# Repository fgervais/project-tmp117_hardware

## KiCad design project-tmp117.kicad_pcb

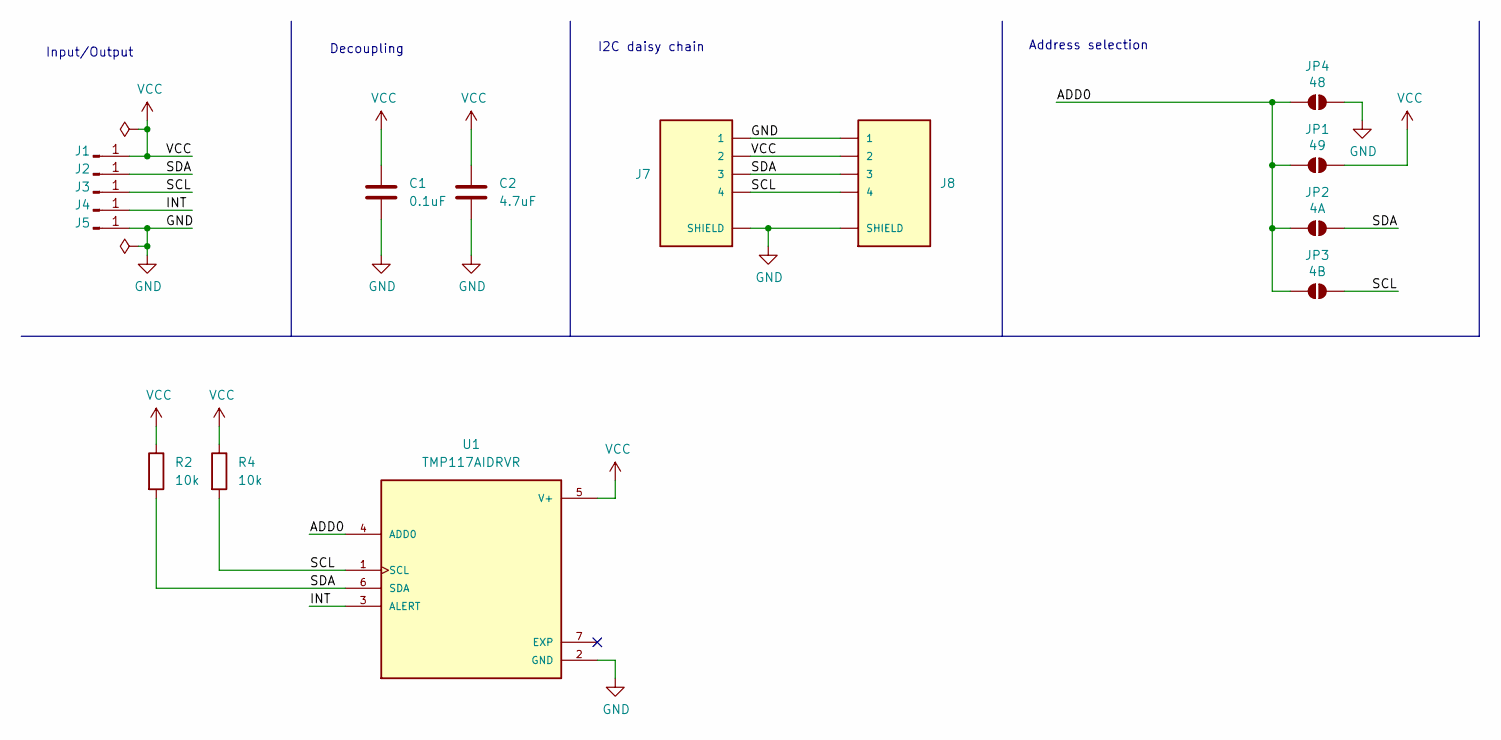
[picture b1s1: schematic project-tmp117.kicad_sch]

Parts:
C1: 0.1uF; C_0603_1608Metric
C2: 4.7uF; C_0805_2012Metric
J1, J2, J3, J4, J5: Conn_01x01_Pin; SolderWirePad_1x01_SMD_1x2mm
J7, J8: SM04B-SRSS-TB(LF)(SN); JST_SM04B-SRSS-TB(LF)(SN)
JP1: 49; SolderJumper-2_P1.3mm_Open_RoundedPad1.0x1.5mm
JP2: 4A; SolderJumper-2_P1.3mm_Open_RoundedPad1.0x1.5mm
JP3: 4B; SolderJumper-2_P1.3mm_Open_RoundedPad1.0x1.5mm
JP4: 48; SolderJumper-2_P1.3mm_Open_RoundedPad1.0x1.5mm
R2, R4: 10k; R_0603_1608Metric
U1: TMP117AIDRVR; SON65P200X200X80-7N; PARTREV B

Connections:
/ADD0: JP1.1 (A), JP2.1 (A), JP3.1 (A), JP4.1 (A), U1.4 (ADD0)
/INT: J4.1, U1.3 (ALERT)
/SCL: J3.1, J7.4, J8.4, JP3.2 (B), R4.2, U1.1 (SCL)
/SDA: J2.1, J7.3, J8.3, JP2.2 (B), R2.2, U1.6 (SDA)
GND: C1.2, C2.2, J5.1, J7.1, J7.S1 (SHIELD), J7.S2 (SHIELD), J8.1, J8.S1 (SHIELD), J8.S2 (SHIELD), JP4.2 (B), U1.2 (GND)
VCC: C1.1, C2.1, J1.1, J7.2, J8.2, JP1.2 (B), R2.1, R4.1, U1.5 (V+)

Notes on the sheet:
Address selection
Input/Output
I2C daisy chain
Decoupling

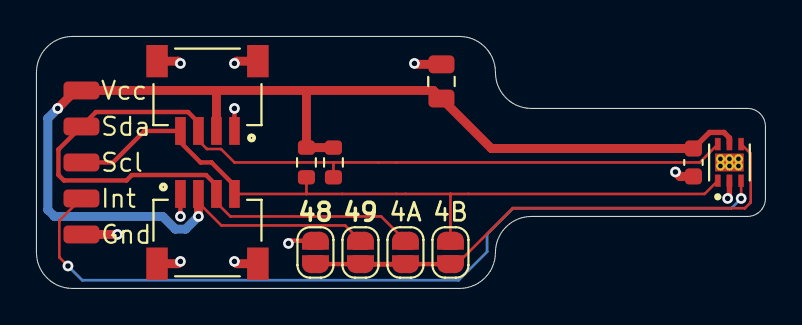
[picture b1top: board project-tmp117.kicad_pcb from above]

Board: 2 copper layers, 40.5 x 14.0 mm, 16 parts (0 on the bottom side), 6 nets.

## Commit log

2024-04-01 Update libraries
2024-04-01 Add a black kicad project
2024-04-01 Add TMP117AIDRVR
2024-04-02 First schematic draft
2024-04-02 Bring everything on board
2024-04-02 First placement
2024-04-02 Routing in progress
2024-04-02 Add a jumper for address 0x48
2024-04-02 Remove the ALERT pull-up
2024-04-02 First routing ready
2024-04-02 Add header silkscreen
2024-04-02 Move silkscreen
2024-04-03 Add version
2024-04-03 Add schematic and assembly files
2024-05-04 Add overview image
2024-05-04 Rename image
